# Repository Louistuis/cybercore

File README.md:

# CyberCore

**Open-hardware proof of concept: a slim black box that runs a frontier open LLM (DeepSeek V3.1, 671B) at home.**

CyberCore is a set of KiCad designs, each generated by a script so every choice is written down. Each one says plainly what is real and what is still a placeholder.

| Part | What | State |
|---|---|---|
| [**console/**](console/) | **CyberCore Console** carrier: 4 × NVIDIA Jetson T5000 (AGX Thor), 512 GB total, 25G mesh between modules, NVMe per module, QSFP28 uplink, 12-layer black board | rev 0.2 PoC: real pin map, Molex and SFF connector grids, TI power stage, **fully routed** (0 unconnected; high-speed pairs not yet length-matched), open items listed |
| [**mgmt/**](mgmt/) | **Management board**: ESP32-S3 + I/O expanders that sequence, reset and monitor the 4 modules over ribbon cables, 4 module consoles on one USB-C | Designed, every signal level sourced from NVIDIA's docs, ERC clean, parts in stock. **Routing not finished** (6 layers, 84 connections open) |
| [**panel/**](panel/) | **Status panel**: ESP32-S3, 16 RGB LEDs, SPI display, USB-C. The console's face | rev 1.0: **routed, DRC clean, every part in stock at JLCPCB, orderable** |
| [**enclosure/**](enclosure/) | **Case**: 252 × 300 × 64 mm, front intake, 4 rear exhaust fans, STL tray + lid | Concept: fit checked, cooling budget by hand calculation |
| [**pcb/**](pcb/) | **CyberCore XL** concept: our own GPU + AMD EPYC with 3.2 TB unified memory, 22 layers | Dream board: the GPU and the AMD socket can't be built or sourced (see why inside) |
| [REAL-BUILD.md](REAL-BUILD.md) | The buy-it-today version: an 8-GPU AMD Instinct server, with power, cooling and cost | Plan |

## How fast?
DeepSeek V3.1 has 671B parameters, of which 37B are active per token. At 4-bit, that's ~400 GB of weights.
- **Console (4 × Thor, 512 GB, 4 × 273 GB/s):** an estimated 10-25 tok/s for one user. It's limited by memory bandwidth: every token has to read ~18.5 GB of weights.
- **Server (8 × AMD MI350X, 2.3 TB, 64 TB/s):** fast enough for many users, but it draws ~10-14 kW.

These are estimates from bandwidth math, not measurements. The PoC is how we find out.

## Tools
- KiCad 10, scripted through its Python (`pcbnew`)
- Freerouting 2.5 for the panel, the console and the management board
- JLCPCB parts API for the stock checks

Each folder's README has its own rebuild steps.

## Not included
NVIDIA's design guide and its pin description spreadsheet are not in this repo. They're a free download from developer.nvidia.com, and `console/make_console.py` reads them from your copy.

## License
CyberCore is **open hardware, and it stays open**.

| What | License |
|---|---|
| Hardware: KiCad boards, footprints, schematics, Gerbers, BOMs, docs | [CERN-OHL-S-2.0](LICENSE) (CERN Open Hardware Licence v2, strongly reciprocal) |
| Software: the Python generator scripts | [GPL-3.0-or-later](LICENSE-SOFTWARE) |
| The CyberCore name and logo | Not licensed: see [TRADEMARKS.md](TRADEMARKS.md) |

What that means:
- **You may** build it, change it and sell it, including commercially.
- **If you ship hardware based on it**, you must publish your modified design files under the same license, keep the credit notices, and print or include the source location.
- **The CyberCore name stays with Louis Studios.** A copy must use its own name.

**Source location:** https://github.com/Louistuis/cybercore

Hardware is provided as is: each README lists the dimensions that are not confirmed yet, so check them before you order anything.

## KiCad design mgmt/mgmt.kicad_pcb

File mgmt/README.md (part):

# CyberCore management board (rev 1.0)

The console's power and reset controller: a small black board that plugs into the **CyberCore Console** carrier with five 40-way ribbon cables.
- It switches each Jetson T5000 module on and off in NVIDIA's order.
- It holds modules in reset or recovery, and watches power-good, current and temperature.
- It gives you all four module debug consoles over one USB-C cable.

The console carrier has no logic of its own; this board is its brain.

## What it does
| Block | Parts | What it does |
|---|---|---|
| Brain | ESP32-S3-WROOM-1-N16R8 (C2913202) | Runs the sequencing in [SEQUENCING.md](SEQUENCING.md). Wi-Fi status page, USB-C (MCU) for firmware and a serial console |
| Control outputs | 5 × TCA9535PWR I/O expanders (C130204), 0x20-0x23 one per module, 0x24 system | Hold every enable and request. An ESP32 reset or firmware update never drops a running module, because the expanders stay powered and keep their outputs |
| Power-bad | 74LVC07A (C7809) per module, wired-AND | `VDDIN_PWR_BAD_N` is released only when the module's HV eFuse PG **and** MV eFuse PG **and** the firmware all agree. A dropping eFuse flags power-bad in hardware, with no firmware in the loop |
| Power-on | SN74AHCT1G08 (C113521) per module on a 5 V always-on rail | Drives `MODULE_POWER_ON` at 5 V like NVIDIA's reference (DG-12084 fig 5-7), and only while `VDDIN_PWR_BAD_N` is high |
| Reset, recovery, thermal request | 74LVC07A open-drain channels, 74LVC1G07 (C7829) | Pull `SYS_RESET_N`, `FORCE_RECOVERY_N`, `THERM_SHDN_REQ_N` low. They can only pull down, never drive a level |
| Reading the module | 2 × SN74LV4T125PWR (C90755) per module | Input-only buffers with a 1.35 V threshold and 5.5 V-tolerant inputs: they read the 1.8 V, 3.3 V and 5 V module outputs, and never feed current into a powered-down module |
| 1.8 V I/O guard | TPS22918 (C131941) per module, driven by that module's own `SYS_RESET_N` | Makes `M<m>_VIO`, the only 1.8 V source that touches the module. It is off whenever the module is in reset (NVIDIA DS-11945 table 6-2) |
| Debug UARTs | CH344Q (C2988084) on USB-C (CONSOLES) + SN74LV1T34 (C100024) per module | 4 module consoles as 4 serial ports, no firmware involved. The ESP32 listens on all four for its log |
| Module I2C | PCA9306DCUR (C33196) per module | 1.8 V module I2C3 ↔ the 3.3 V system bus (PMBus + QSFP28). Each module can be switched off the bus |
| Current | ESP32 ADC1 × 4, 10k + 100 nF per channel | HV eFuse current monitors: 1.16 V at 10 A, 1.55 V at the 13.4 A limit |
| Power | TLV75518 (C2877863) 1.8 V, TPS61222 (C116461) 5 V, both from the console's 3.3 V standby | The board takes nothing from USB, so it can never back-feed the console |
| Extras | Qwiic port (inlet temperature sensor), RESET / BOOT buttons, heartbeat LED, 4 × M3 holes | |

## Connections to the console
- **Headers:** 5 × 2×20 1.27 mm (C71827, through-hole), with the same reference designators as on the console:
  - J20-J23: modules 0-3
  - J4: SYS
- **Cables:** IDC ribbon, pin 1 to pin 1, so the pinout is identical on both ends. Odd pins carry the signals listed in `parts.py` (`MGMT` and `SYS`, copied from `console/make_console.py`); even pins are GND.
- **Power:** the board runs from the console's 3.3 V standby rail on pin 39 of every header (about 0.4 A peak with Wi-Fi transmitting).

## Signal levels: every decision and its source
| Module pin | NVIDIA says | This board | Source |
|---|---|---|---|
| MODULE_POWER_ON | Input, CMOS 5.0 V, driven low first | 5 V AND gate (5V_AO) + 100 Ω, 100k pull-down | DG-12084 table 5-1, fig 5-2 note 2, fig 5-7 / table 5-2 (5V_AO gate, PP) |
| CARRIER_POWER_ON | Output, open drain 3.3 V, 10k pull-up on module | Read directly by the expander (3.3 V), 100k pull-down | DG table 5-1 |
| SYS_RESET_N | Bidir, open drain 1.8 V, 10k to 1.8 V on module | Read via LV4T125; pulled low by a 74LVC07; drives the VIO switch; 470k pull-down | DG table 5-1, DS table 3-1 |
| VDDIN_PWR_BAD_N | Open drain 5.0 V, 10k to 5 V on module | Three 74LVC07 outputs wired-AND (HV_PG, MV_PG, firmware); read via LV4T125 (5.5 V tolerant) | DG table 5-1, 5.1.1, 5.1.4 |
| FORCE_RECOVERY_N | Input, CMOS 1.8 V, 20k to 1.8 V on module | 74LVC07 open drain only | DG table 5-1, fig 18-1, ch 18 |
| MODULE_SHDN_N | Output, CMOS 1.8 V, 10k to 1.8 V on module | Read via LV4T125 | DG table 5-1 |
| THERM_ALERT_N | Open drain "3.3 V" (DG, DS), but the schematic checklist lists a 10k pull-up to 1.8 V on the module | Read via LV4T125 (works for either level), 100k to M<m>_VIO | DG table 5-1, DS table 3-1, Schematic Checklist v1.1 "Module_Signal_Term" |
| THERM_SHDN_REQ_N | **Not described** (only in the pin spreadsheet, G59) | Read via LV4T125 + 74LVC07 pull-down, 100k to VIO; firmware leaves it alone | Pin Descriptions v1.0 only |
| MODULE_POWER_GOOD | **Not described** (only in the pin spreadsheet, L59) | Read only via LV4T125, 100k pull-down | Pin Descriptions v1.0 only |
| PRSNT0 / PRSNT1 | Tied together on the module | PRSNT0 = GND, PRSNT1 10k to 3.3 V, read (low = seated) | DG table 5-1, fig 5-7 (PRSNT1 to 3V3_AO) |
| UART3_TX_DEBUG | Output, CMOS 1.8 V | Read via LV4T125 into the CH344Q, 100k to VIO | DG 17.2.2, table 17-3 |
| UART3_RX_DEBUG | Input, 1.8 V | SN74LV1T34 powered from VIO (off in reset, Ioff), 100 Ω; 100k pull-up on the 3.3 V side | DG table 17-3 |
| I2C3_CLK / DAT | Open drain 1.8 V, 1k to 1.8 V on module | PCA9306, VREF1 = VIO, enable through 74LVC1G07 | DG table 12-2, SP-12533 |
| HV_EN, MV_EN, SV_EN, BUCK5_EN | eFuse EN/UVLO 1.2 V (max 7 V), TPS22918 ON 1.0 V, TPS546B24A EN (max 5.5 V); 100k pull-downs on the console | 3.3 V push-pull from the expanders | TPS25982, TPS22918, TPS546B24A data sheets |
| HV_PG, MV_PG, BUCK5_PG | Open drain, 10k to 3.3 V on the console | Read directly + feed the power-bad AND | console/make_console.py |
| HV_IMON | 246 uA/A × 470 Ω | 10k + 100 nF into ESP32 ADC1 (0-3.1 V at 12 dB) | TPS25982 7.3.5 (10k series recommended) |
| QSFP sideband | 3.3 V LVTTL | Direct; 10k host pull-ups on ModPrsL and IntL | SFF-8679 |

**The one rule behind the table:** no 1.8 V module input is ever driven high while that module's `SYS_RESET_N` is low (DS-11945 table 6-2, VM_PIN).
- The only push-pull driver into a 1.8 V module input, and every 1.8 V pull-up, sit on `M<m>_VIO`.
- A load switch turns `M<m>_VIO` on from the module's own `SYS_RESET_N`, and off within ~15 µs when it falls.

## Board
- 132 × 72 mm, **6 layers** (F.Cu signal + GND, In1.Cu GND plane, In2.Cu and In3.Cu signal, In4.Cu 3V3 plane, B.Cu signal + GND), 1.6 mm, **black solder mask, white silk, ENIG**, all parts on top. It started as 4 layers, but Freerouting could not finish that at this size.
- **Rules:** JLCPCB standard 6-layer (0.127 mm track and space, 0.5 / 0.25 mm vias).
- **Routing:** Freerouting.
- **DRC:** see `drc.rpt`. **ERC:** see `erc.rpt`. Results are listed under "State" below.

## State
**Real:**
- Every pin of every part, from its maker's data sheet (TI, WCH, Espressif). The pin tables are quoted in `parts.py`.
- The console interface, copied from `console/make_console.py`.
- Every signal level, checked against NVIDIA's documents (table above).
- Every part was in stock at JLCPCB on 2026-11-17 (`jlc/stock.csv`).

**Routing is not finished.** After three Freerouting runs, 84 connections are still open and about 40 tracks are necked to 0.095 mm (JLC's minimum is 0.09). `mgmt_routed.kicad_pcb` is the work in progress: finish it by hand in KiCad, or give the board more room.

**Not verified (check before ordering):**
- `THERM_SHDN_REQ_N` and `MODULE_POWER_GOOD` are only names in NVIDIA's pin spreadsheet. The board treats them safely (read, plus an optional pull-down), but their function is unknown.
- `THERM_ALERT_N`: the design guide says 3.3 V open drain, the checklist says a 1.8 V pull-up. Both levels work here.
- `MODULE_POWER_ON` VIH is not published. The board drives 5 V as NVIDIA's reference does, so the number does not matter.
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
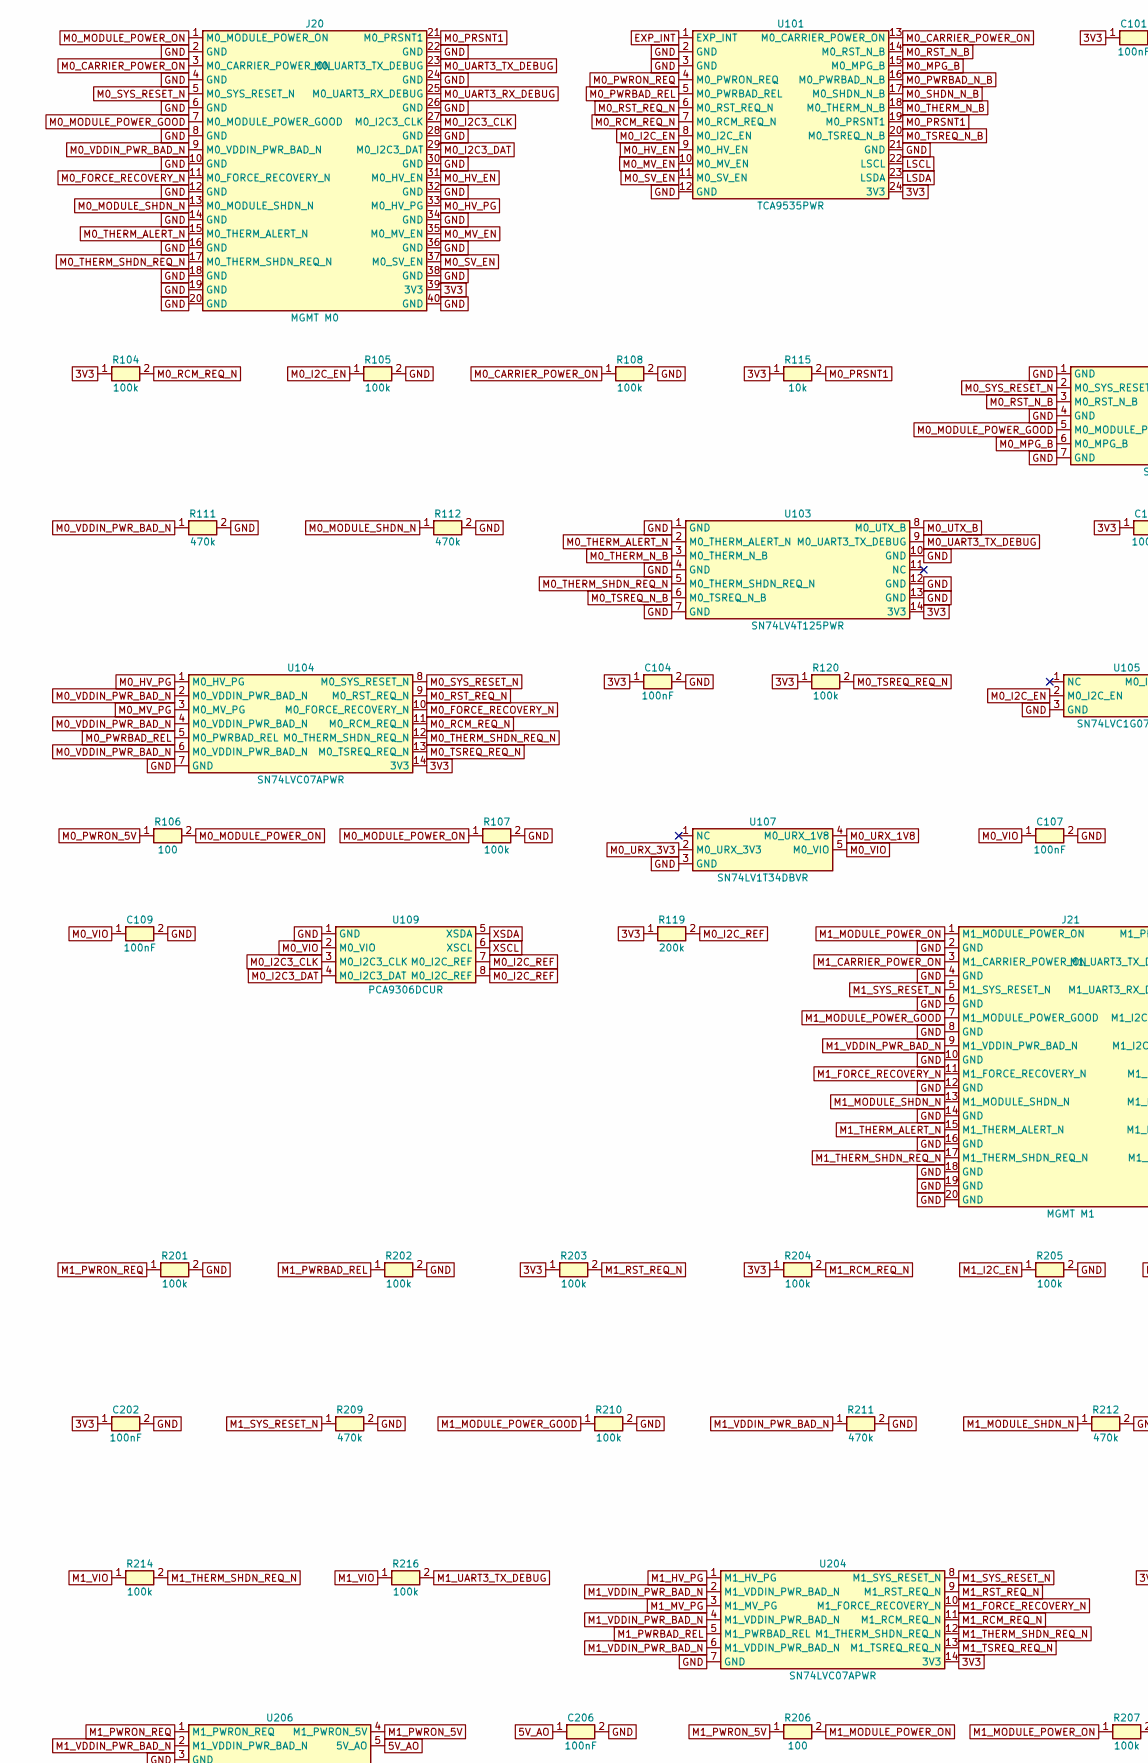
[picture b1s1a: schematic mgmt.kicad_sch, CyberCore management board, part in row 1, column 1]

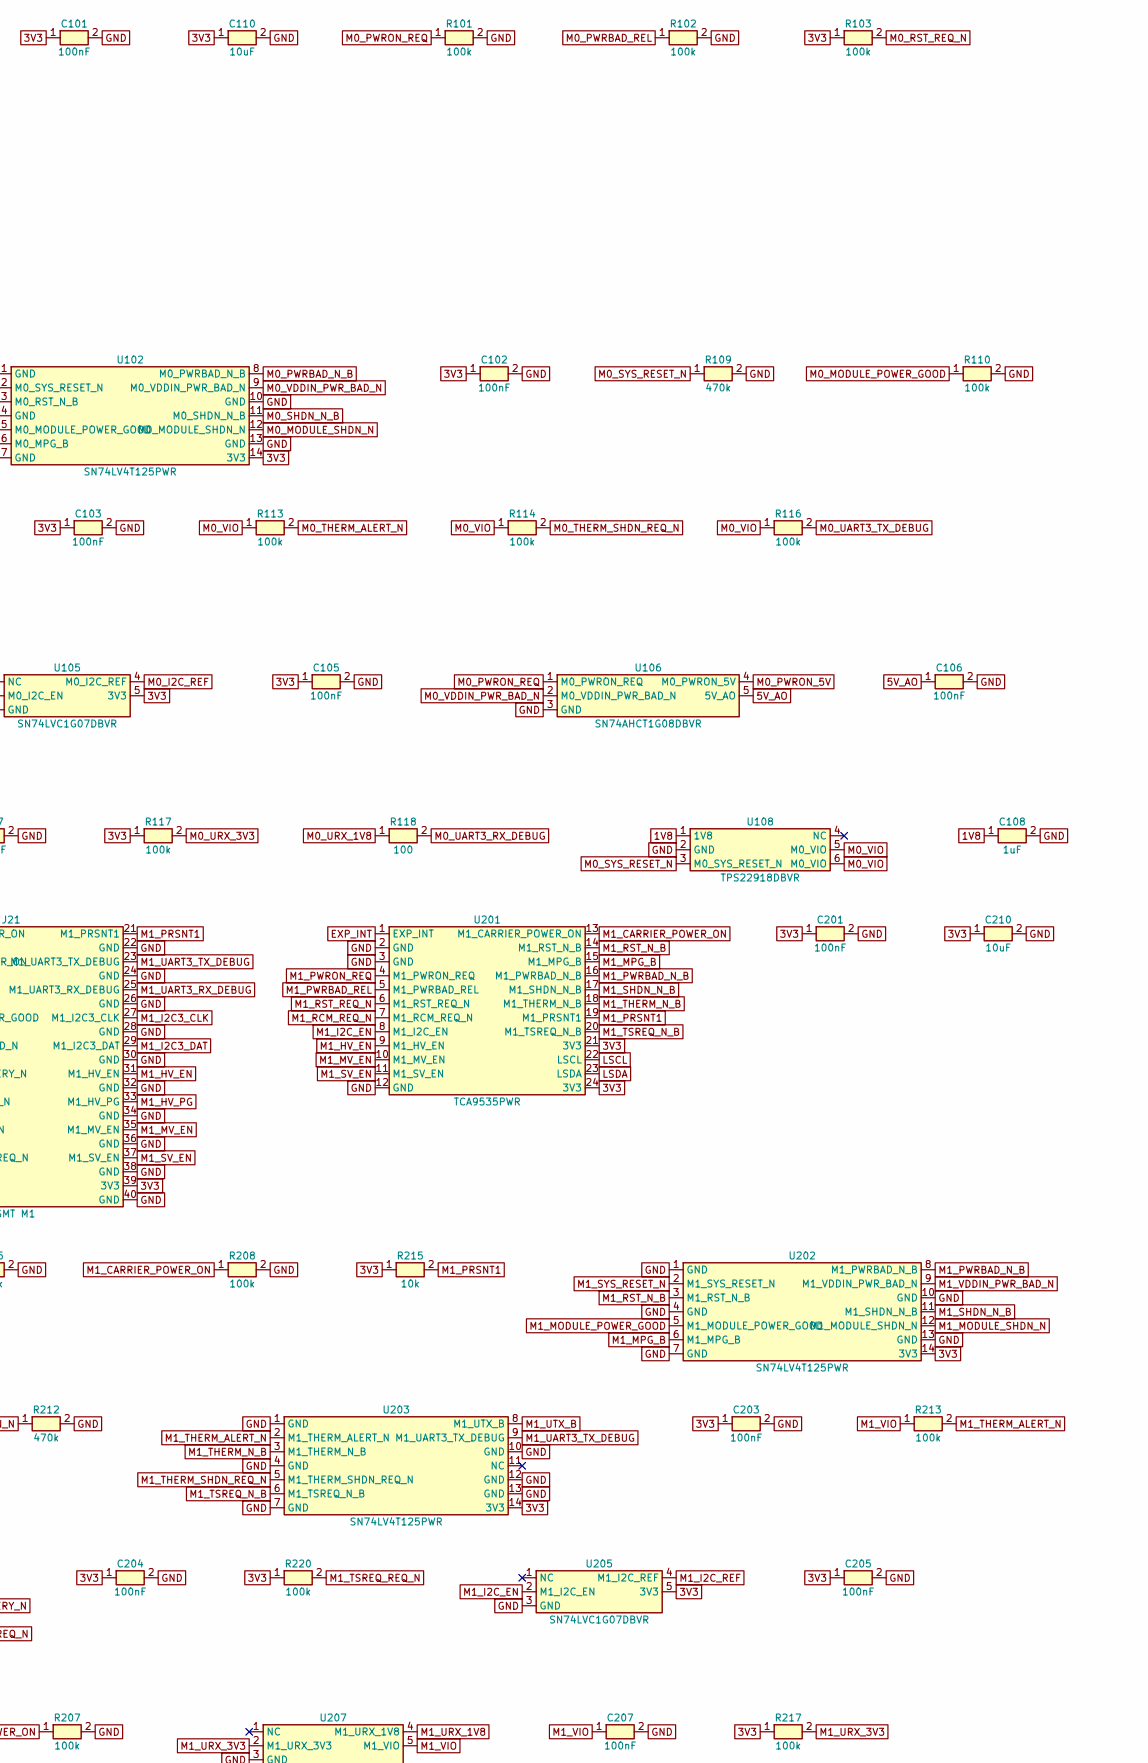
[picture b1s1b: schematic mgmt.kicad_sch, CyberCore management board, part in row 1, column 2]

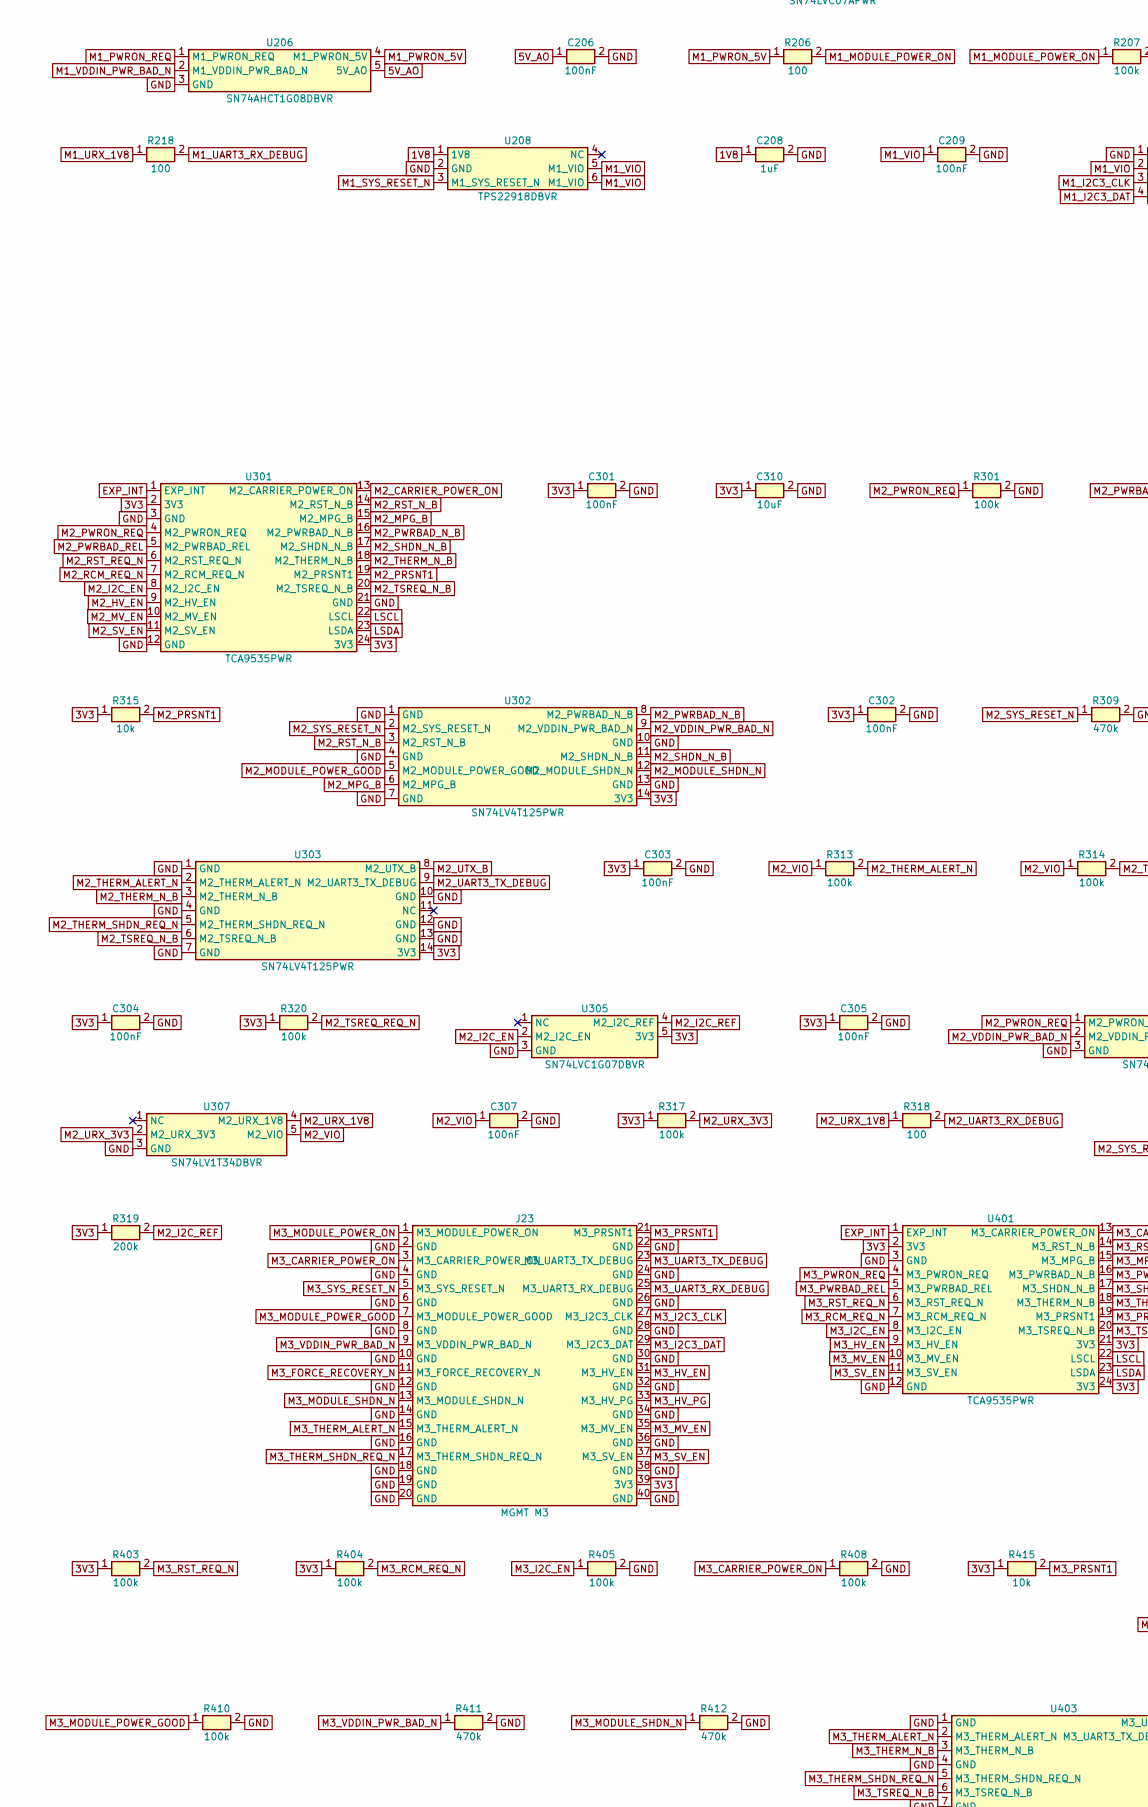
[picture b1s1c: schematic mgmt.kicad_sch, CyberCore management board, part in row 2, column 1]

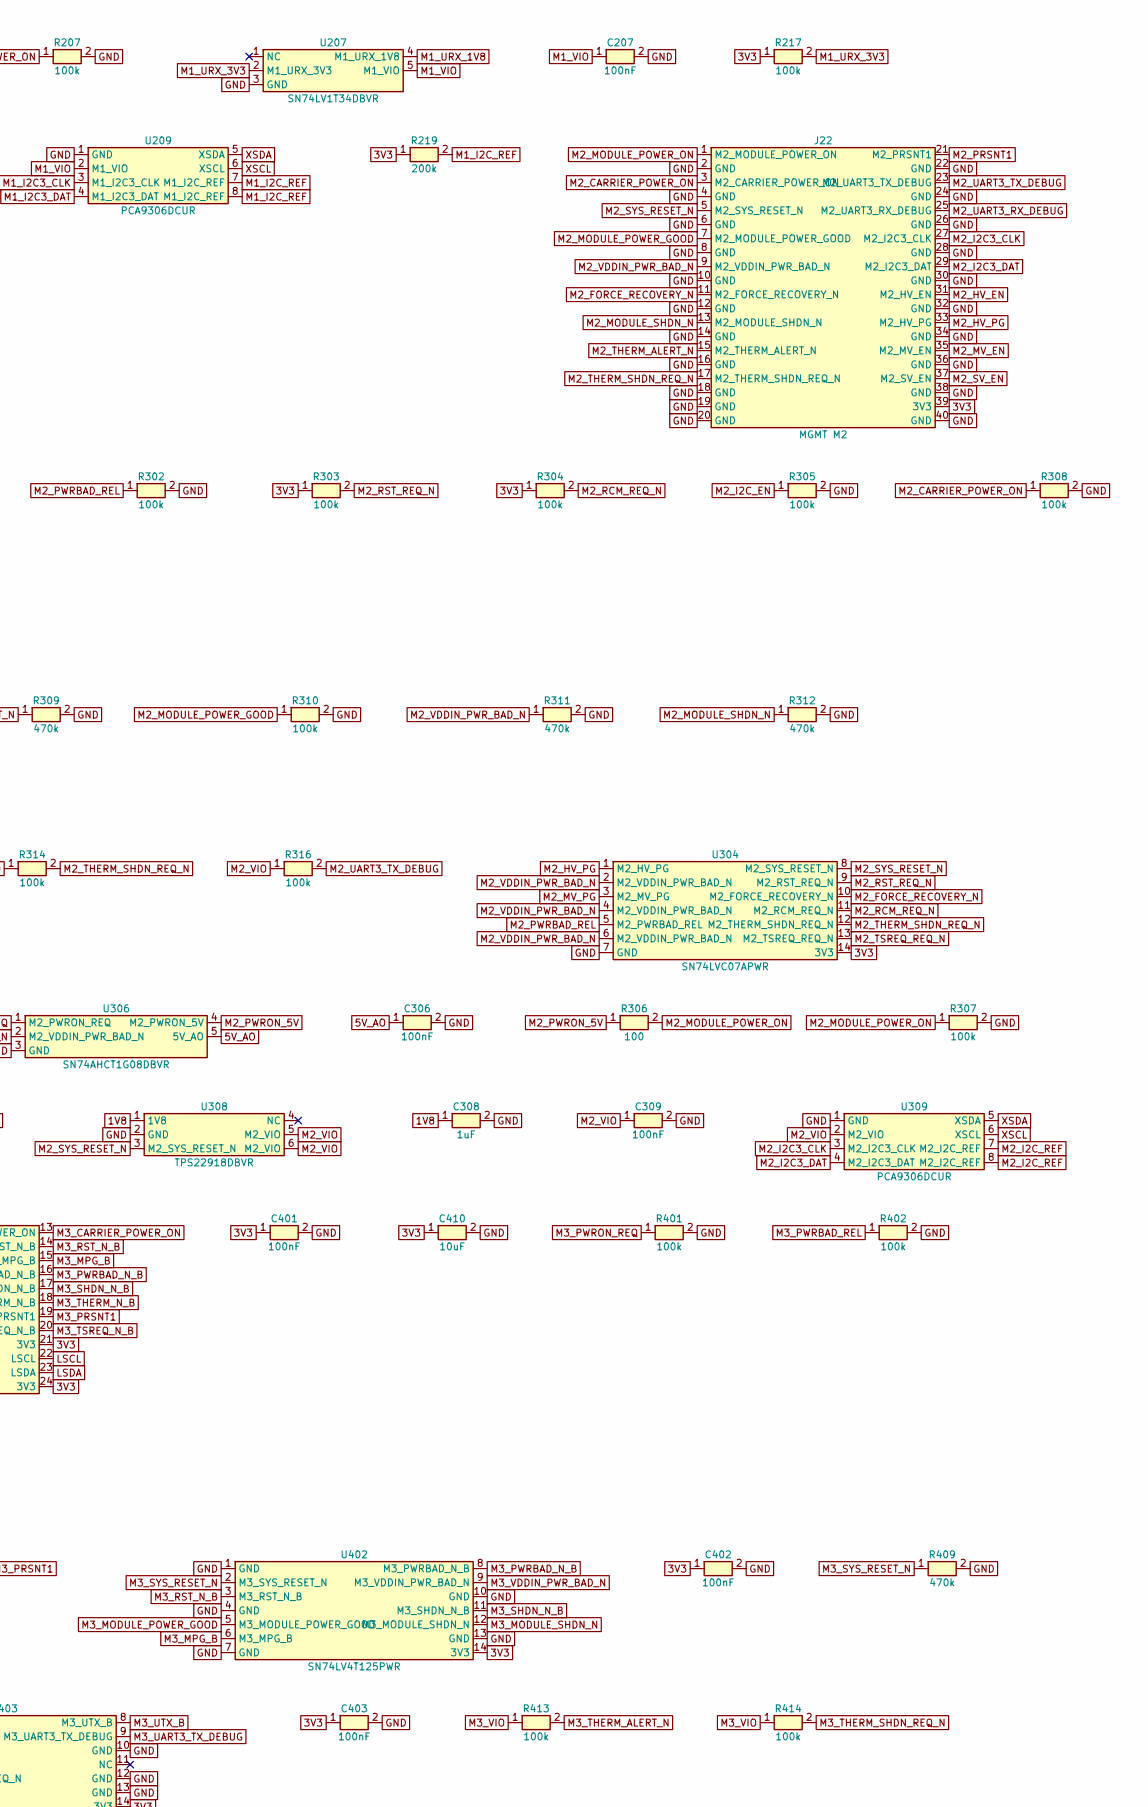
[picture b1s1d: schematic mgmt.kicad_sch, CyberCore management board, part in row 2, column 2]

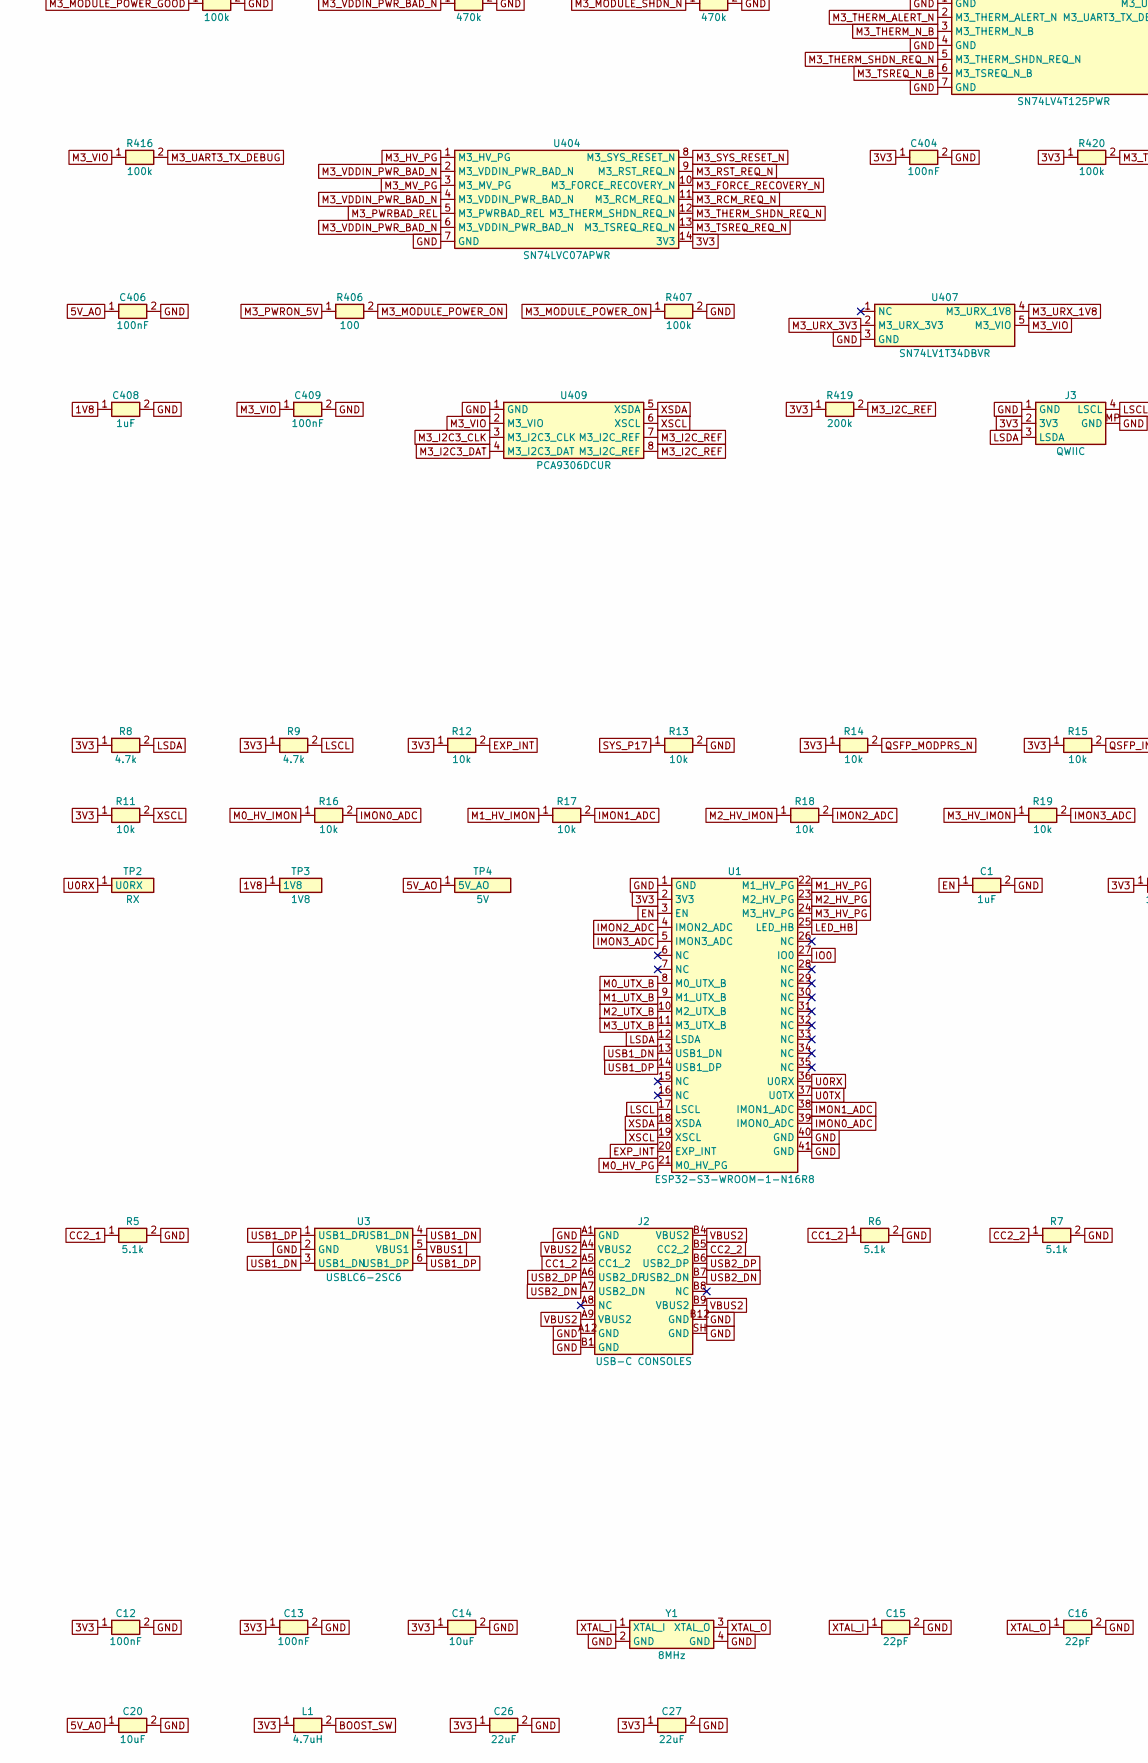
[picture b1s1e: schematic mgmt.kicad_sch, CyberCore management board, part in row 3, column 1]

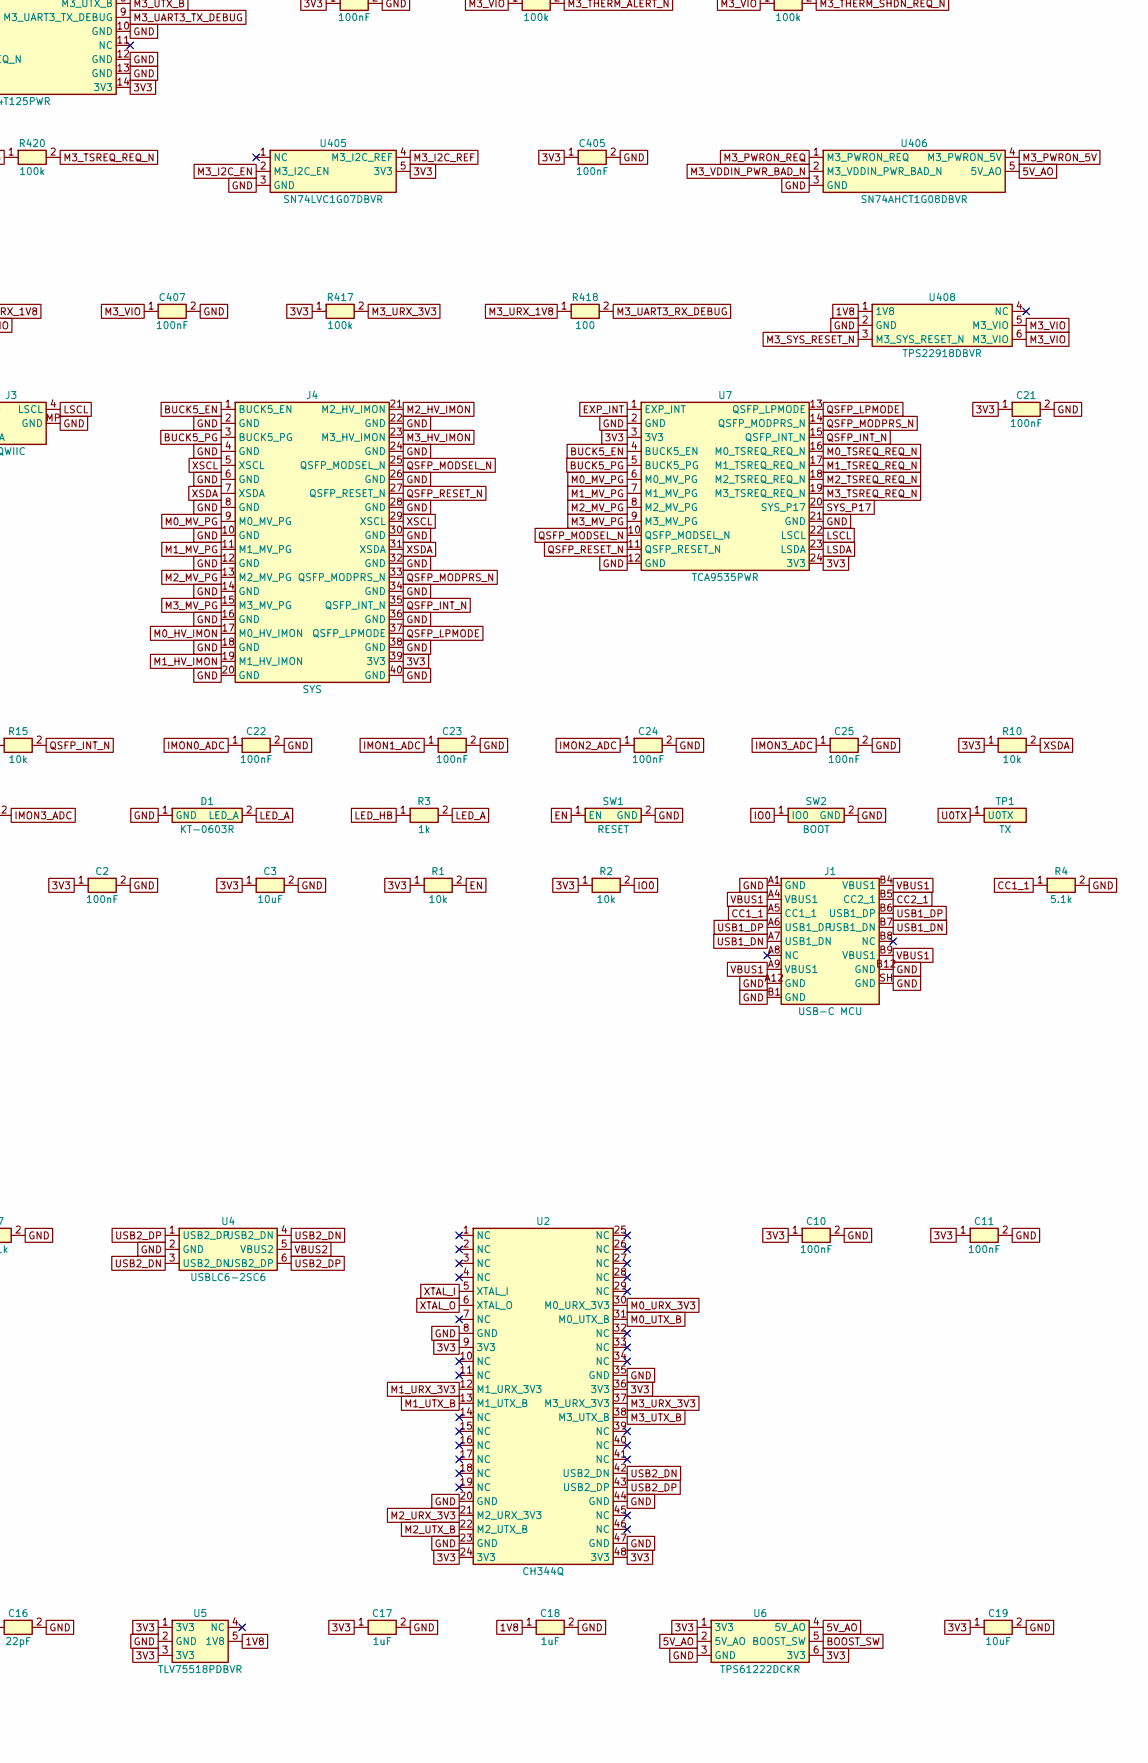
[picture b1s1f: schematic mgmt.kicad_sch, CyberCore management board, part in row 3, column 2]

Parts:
C1, C17, C18, C108, C208, C308, C408: 1uF; C_0402_1005Metric; LCSC C52923
C2, C10, C11, C12, C13, C21, C22, C23, C24, C25, C101, C102, C103, C104, C105, C106, C107, C109, C201, C202, C203, C204, C205, C206, C207, C209, C301, C302, C303, C304, C305, C306, C307, C309, C401, C402, C403, C404, C405, C406, C407, C409: 100nF; C_0402_1005Metric; LCSC C1525
C3, C14, C19, C20, C110, C210, C310, C410: 10uF; C_0603_1608Metric; LCSC C19702
C15, C16: 22pF; C_0402_1005Metric; LCSC C1555
C26, C27: 22uF; C_0805_2012Metric; LCSC C45783
D1: KT-0603R; LED_0603_1608Metric; LCSC C2286
J1: USB-C MCU; USB_C_Receptacle_HRO_TYPE-C-31-M-12; LCSC C165948
J2: USB-C CONSOLES; USB_C_Receptacle_HRO_TYPE-C-31-M-12; LCSC C165948
J3: QWIIC; JST_SH_SM04B-SRSS-TB_1x04-1MP_P1.00mm_Horizontal; LCSC C160404
J4: SYS; PinHeader_2x20_P1.27mm_Vertical; LCSC C71827
J20: MGMT M0; PinHeader_2x20_P1.27mm_Vertical; LCSC C71827
J21: MGMT M1; PinHeader_2x20_P1.27mm_Vertical; LCSC C71827
J22: MGMT M2; PinHeader_2x20_P1.27mm_Vertical; LCSC C71827
J23: MGMT M3; PinHeader_2x20_P1.27mm_Vertical; LCSC C71827
L1: 4.7uH; L_1008_2520Metric; LCSC C66536
R1, R2, R10, R11, R12, R13, R14, R15, R16, R17, R18, R19, R115, R215, R315, R415: 10k; R_0402_1005Metric; LCSC C25744
R3: 1k; R_0402_1005Metric; LCSC C11702
R4, R5, R6, R7: 5.1k; R_0402_1005Metric; LCSC C25905
R8, R9: 4.7k; R_0402_1005Metric; LCSC C25900
R101, R102, R103, R104, R105, R107, R108, R110, R113, R114, R116, R117, R120, R201, R202, R203, R204, R205, R207, R208, R210, R213, R214, R216, R217, R220, R301, R302, R303, R304, R305, R307, R308, R310, R313, R314, R316, R317, R320, R401, R402, R403, R404, R405, R407, R408, R410, R413, R414, R416, R417, R420: 100k; R_0402_1005Metric; LCSC C25741
R106, R118, R206, R218, R306, R318, R406, R418: 100; R_0402_1005Metric; LCSC C25076
R109, R111, R112, R209, R211, R212, R309, R311, R312, R409, R411, R412: 470k; R_0402_1005Metric; LCSC C25790
R119, R219, R319, R419: 200k; R_0402_1005Metric; LCSC C25764
SW1: RESET; SW_Push_1P1T_XKB_TS-1187A; LCSC C318884
SW2: BOOT; SW_Push_1P1T_XKB_TS-1187A; LCSC C318884
TP1: TX; TestPoint_Pad_D1.0mm
TP2: RX; TestPoint_Pad_D1.0mm
TP3: 1V8; TestPoint_Pad_D1.0mm
TP4: 5V; TestPoint_Pad_D1.0mm
U1: ESP32-S3-WROOM-1-N16R8; ESP32-S3-WROOM-1; LCSC C2913202
U2: CH344Q; LQFP-48_7x7mm_P0.5mm; LCSC C2988084
U3, U4: USBLC6-2SC6; SOT-23-6; LCSC C7519
U5: TLV75518PDBVR; SOT-23-5; LCSC C2877863
U6: TPS61222DCKR; SOT-363_SC-70-6; LCSC C116461
U7, U101, U201, U301, U401: TCA9535PWR; TSSOP-24_4.4x7.8mm_P0.65mm; LCSC C130204
U102, U103, U202, U203, U302, U303, U402, U403: SN74LV4T125PWR; TSSOP-14_4.4x5mm_P0.65mm; LCSC C90755
U104, U204, U304, U404: SN74LVC07APWR; TSSOP-14_4.4x5mm_P0.65mm; LCSC C7809
U105, U205, U305, U405: SN74LVC1G07DBVR; SOT-23-5; LCSC C7829
U106, U206, U306, U406: SN74AHCT1G08DBVR; SOT-23-5; LCSC C113521
U107, U207, U307, U407: SN74LV1T34DBVR; SOT-23-5; LCSC C100024
U108, U208, U308, U408: TPS22918DBVR; SOT-23-6; LCSC C131941
U109, U209, U309, U409: PCA9306DCUR; VSSOP-8_2.3x2mm_P0.5mm; LCSC C33196
Y1: 8MHz; Crystal_SMD_3225-4Pin_3.2x2.5mm; LCSC C5181477

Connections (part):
1V8: C18.1, C108.1, C208.1, C308.1, C408.1, TP3.1, U5.5 (1V8), U108.1 (1V8), U208.1 (1V8), U308.1 (1V8), U408.1 (1V8); also elsewhere on the board
3V3: C2.1, C3.1, C10.1, C11.1, C12.1, C13.1, C14.1, C17.1, C19.1, C21.1, C26.1, C27.1, C101.1, C102.1, C103.1, C104.1, C105.1, C110.1, C201.1, C202.1, C203.1, C204.1, C205.1, C210.1, C301.1, C302.1, C303.1, C304.1, C305.1, C310.1, C401.1, C402.1, C403.1, C404.1, C405.1, C410.1, J3.2 (3V3), J4.39 (3V3), J20.39 (3V3), J21.39 (3V3), J22.39 (3V3), J23.39 (3V3), L1.1, R1.1, R2.1, R8.1, R9.1, R10.1, R11.1, R12.1, R14.1, R15.1, R103.1, R104.1, R115.1, R117.1, R119.1, R120.1, R203.1, R204.1, R215.1, R217.1, R219.1, R220.1, R303.1, R304.1, R315.1, R317.1, R319.1, R320.1, R403.1, R404.1, R415.1, R417.1, R419.1, R420.1, U1.2 (3V3), U2.9 (3V3), U2.24 (3V3), U2.36 (3V3), U2.48 (3V3), U5.1 (3V3)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
5V_AO: C20.1, C106.1, C206.1, C306.1, C406.1, TP4.1, U6.2 (5V_AO), U6.4 (5V_AO), U106.5 (5V_AO), U206.5 (5V_AO), U306.5 (5V_AO), U406.5 (5V_AO)
BOOST_SW: L1.2, U6.5 (BOOST_SW)
BUCK5_EN: J4.1 (BUCK5_EN), U7.4 (BUCK5_EN)
BUCK5_PG: J4.3 (BUCK5_PG), U7.5 (BUCK5_PG)
CC1_1: J1.A5 (CC1_1), R4.1
CC1_2: J2.A5 (CC1_2), R6.1
CC2_1: J1.B5 (CC2_1), R5.1
CC2_2: J2.B5 (CC2_2), R7.1
EN: C1.1, R1.2, SW1.1 (EN), U1.3 (EN)
EXP_INT: R12.2, U1.20 (EXP_INT), U7.1 (EXP_INT), U101.1 (EXP_INT), U201.1 (EXP_INT), U301.1 (EXP_INT), U401.1 (EXP_INT)
GND: C1.2, C2.2, C3.2, C10.2, C11.2, C12.2, C13.2, C14.2, C15.2, C16.2, C17.2, C18.2, C19.2, C20.2, C21.2, C22.2, C23.2, C24.2, C25.2, C26.2, C27.2, C101.2, C102.2, C103.2, C104.2, C105.2, C106.2, C107.2, C108.2, C109.2, C110.2, C201.2, C202.2, C203.2, C204.2, C205.2, C206.2, C207.2, C208.2, C209.2, C210.2, C301.2, C302.2, C303.2, C304.2, C305.2, C306.2, C307.2, C308.2, C309.2, C310.2, C401.2, C402.2, C403.2, C404.2, C405.2, C406.2, C407.2, C408.2, C409.2, C410.2, D1.1 (GND), J1.A1 (GND), J1.A12 (GND), J1.B1 (GND), J1.B12 (GND), J1.SH (GND), J2.A1 (GND), J2.A12 (GND), J2.B1 (GND), J2.B12 (GND), J2.SH (GND), J3.1 (GND), J3.MP (GND), J4.2 (GND), J4.4 (GND), J4.6 (GND), J4.8 (GND), J4.10 (GND), J4.12 (GND), J4.14 (GND), J4.16 (GND)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; also elsewhere on the board
IMON0_ADC: C22.1, R16.2, U1.39 (IMON0_ADC)
IMON1_ADC: C23.1, R17.2, U1.38 (IMON1_ADC)
IMON2_ADC: C24.1, R18.2, U1.4 (IMON2_ADC)
IMON3_ADC: C25.1, R19.2, U1.5 (IMON3_ADC)
IO0: R2.2, SW2.1 (IO0), U1.27 (IO0)
LED_A: D1.2 (LED_A), R3.2
LED_HB: R3.1, U1.25 (LED_HB)
LSCL: J3.4 (LSCL), R9.2, U1.17 (LSCL), U7.22 (LSCL), U101.22 (LSCL), U201.22 (LSCL), U301.22 (LSCL), U401.22 (LSCL)
LSDA: J3.3 (LSDA), R8.2, U1.12 (LSDA), U7.23 (LSDA), U101.23 (LSDA), U201.23 (LSDA), U301.23 (LSDA), U401.23 (LSDA)
M0_CARRIER_POWER_ON: J20.3 (M0_CARRIER_POWER_ON), R108.1, U101.13 (M0_CARRIER_POWER_ON)
M0_FORCE_RECOVERY_N: J20.11 (M0_FORCE_RECOVERY_N), U104.10 (M0_FORCE_RECOVERY_N)
M0_HV_EN: J20.31 (M0_HV_EN), U101.9 (M0_HV_EN)
M0_HV_IMON: J4.17 (M0_HV_IMON), R16.1
M0_HV_PG: J20.33 (M0_HV_PG), U1.21 (M0_HV_PG), U104.1 (M0_HV_PG)
M0_I2C3_CLK: J20.27 (M0_I2C3_CLK), U109.3 (M0_I2C3_CLK)
M0_I2C3_DAT: J20.29 (M0_I2C3_DAT), U109.4 (M0_I2C3_DAT)
M0_I2C_EN: R105.1, U101.8 (M0_I2C_EN), U105.2 (M0_I2C_EN)
M0_I2C_REF: R119.2, U105.4 (M0_I2C_REF), U109.7 (M0_I2C_REF), U109.8 (M0_I2C_REF)
M0_MODULE_POWER_GOOD: J20.7 (M0_MODULE_POWER_GOOD), R110.1, U102.5 (M0_MODULE_POWER_GOOD)
M0_MODULE_POWER_ON: J20.1 (M0_MODULE_POWER_ON), R106.2, R107.1
M0_MODULE_SHDN_N: J20.13 (M0_MODULE_SHDN_N), R112.1, U102.12 (M0_MODULE_SHDN_N)
M0_MPG_B: U101.15 (M0_MPG_B), U102.6 (M0_MPG_B)
M0_MV_EN: J20.35 (M0_MV_EN), U101.10 (M0_MV_EN)
M0_MV_PG: J4.9 (M0_MV_PG), U7.6 (M0_MV_PG), U104.3 (M0_MV_PG)
M0_PRSNT1: J20.21 (M0_PRSNT1), R115.2, U101.19 (M0_PRSNT1)
M0_PWRBAD_N_B: U101.16 (M0_PWRBAD_N_B), U102.8 (M0_PWRBAD_N_B)
M0_PWRBAD_REL: R102.1, U101.5 (M0_PWRBAD_REL), U104.5 (M0_PWRBAD_REL)
M0_PWRON_5V: R106.1, U106.4 (M0_PWRON_5V)
M0_PWRON_REQ: R101.1, U101.4 (M0_PWRON_REQ), U106.1 (M0_PWRON_REQ)
M0_RCM_REQ_N: R104.2, U101.7 (M0_RCM_REQ_N), U104.11 (M0_RCM_REQ_N)
M0_RST_N_B: U101.14 (M0_RST_N_B), U102.3 (M0_RST_N_B)
M0_RST_REQ_N: R103.2, U101.6 (M0_RST_REQ_N), U104.9 (M0_RST_REQ_N)
M0_SHDN_N_B: U101.17 (M0_SHDN_N_B), U102.11 (M0_SHDN_N_B)
M0_SV_EN: J20.37 (M0_SV_EN), U101.11 (M0_SV_EN)
M0_SYS_RESET_N: J20.5 (M0_SYS_RESET_N), R109.1, U102.2 (M0_SYS_RESET_N), U104.8 (M0_SYS_RESET_N), U108.3 (M0_SYS_RESET_N)
M0_THERM_ALERT_N: J20.15 (M0_THERM_ALERT_N), R113.2, U103.2 (M0_THERM_ALERT_N)
M0_THERM_N_B: U101.18 (M0_THERM_N_B), U103.3 (M0_THERM_N_B)
M0_THERM_SHDN_REQ_N: J20.17 (M0_THERM_SHDN_REQ_N), R114.2, U103.5 (M0_THERM_SHDN_REQ_N), U104.12 (M0_THERM_SHDN_REQ_N)
M0_TSREQ_N_B: U101.20 (M0_TSREQ_N_B), U103.6 (M0_TSREQ_N_B)
M0_TSREQ_REQ_N: R120.2, U7.16 (M0_TSREQ_REQ_N), U104.13 (M0_TSREQ_REQ_N)
M0_UART3_RX_DEBUG: J20.25 (M0_UART3_RX_DEBUG), R118.2
M0_UART3_TX_DEBUG: J20.23 (M0_UART3_TX_DEBUG), R116.2, U103.9 (M0_UART3_TX_DEBUG)
M0_URX_1V8: R118.1, U107.4 (M0_URX_1V8)
M0_URX_3V3: R117.2, U2.30 (M0_URX_3V3), U107.2 (M0_URX_3V3)
M0_UTX_B: U1.8 (M0_UTX_B), U2.31 (M0_UTX_B), U103.8 (M0_UTX_B)
M0_VDDIN_PWR_BAD_N: J20.9 (M0_VDDIN_PWR_BAD_N), R111.1, U102.9 (M0_VDDIN_PWR_BAD_N), U104.2 (M0_VDDIN_PWR_BAD_N), U104.4 (M0_VDDIN_PWR_BAD_N), U104.6 (M0_VDDIN_PWR_BAD_N), U106.2 (M0_VDDIN_PWR_BAD_N)
M0_VIO: C107.1, C109.1, R113.1, R114.1, R116.1, U107.5 (M0_VIO), U108.5 (M0_VIO), U108.6 (M0_VIO), U109.2 (M0_VIO)
M1_CARRIER_POWER_ON: J21.3 (M1_CARRIER_POWER_ON), R208.1, U201.13 (M1_CARRIER_POWER_ON)
M1_FORCE_RECOVERY_N: J21.11 (M1_FORCE_RECOVERY_N), U204.10 (M1_FORCE_RECOVERY_N)
M1_HV_EN: J21.31 (M1_HV_EN), U201.9 (M1_HV_EN)
M1_HV_IMON: J4.19 (M1_HV_IMON), R17.1
M1_HV_PG: J21.33 (M1_HV_PG), U1.22 (M1_HV_PG), U204.1 (M1_HV_PG)
M1_I2C3_CLK: J21.27 (M1_I2C3_CLK), U209.3 (M1_I2C3_CLK)
M1_I2C3_DAT: J21.29 (M1_I2C3_DAT), U209.4 (M1_I2C3_DAT)
M1_I2C_EN: R205.1, U201.8 (M1_I2C_EN), U205.2 (M1_I2C_EN)
M1_I2C_REF: R219.2, U205.4 (M1_I2C_REF), U209.7 (M1_I2C_REF), U209.8 (M1_I2C_REF)
M1_MODULE_POWER_GOOD: J21.7 (M1_MODULE_POWER_GOOD), R210.1, U202.5 (M1_MODULE_POWER_GOOD)
M1_MODULE_POWER_ON: J21.1 (M1_MODULE_POWER_ON), R206.2, R207.1
M1_MODULE_SHDN_N: J21.13 (M1_MODULE_SHDN_N), R212.1, U202.12 (M1_MODULE_SHDN_N)
M1_MPG_B: U201.15 (M1_MPG_B), U202.6 (M1_MPG_B)
M1_MV_EN: J21.35 (M1_MV_EN), U201.10 (M1_MV_EN)
M1_MV_PG: J4.11 (M1_MV_PG), U7.7 (M1_MV_PG), U204.3 (M1_MV_PG)
M1_PRSNT1: J21.21 (M1_PRSNT1), R215.2, U201.19 (M1_PRSNT1)
M1_PWRBAD_N_B: U201.16 (M1_PWRBAD_N_B), U202.8 (M1_PWRBAD_N_B)
M1_PWRBAD_REL: R202.1, U201.5 (M1_PWRBAD_REL), U204.5 (M1_PWRBAD_REL)
M1_PWRON_5V: R206.1, U206.4 (M1_PWRON_5V)
M1_PWRON_REQ: R201.1, U201.4 (M1_PWRON_REQ), U206.1 (M1_PWRON_REQ)
M1_RCM_REQ_N: R204.2, U201.7 (M1_RCM_REQ_N), U204.11 (M1_RCM_REQ_N)
M1_RST_N_B: U201.14 (M1_RST_N_B), U202.3 (M1_RST_N_B)
M1_RST_REQ_N: R203.2, U201.6 (M1_RST_REQ_N), U204.9 (M1_RST_REQ_N)
M1_SHDN_N_B: U201.17 (M1_SHDN_N_B), U202.11 (M1_SHDN_N_B)
M1_SV_EN: J21.37 (M1_SV_EN), U201.11 (M1_SV_EN)
M1_SYS_RESET_N: J21.5 (M1_SYS_RESET_N), R209.1, U202.2 (M1_SYS_RESET_N), U204.8 (M1_SYS_RESET_N), U208.3 (M1_SYS_RESET_N)
M1_THERM_ALERT_N: J21.15 (M1_THERM_ALERT_N), R213.2, U203.2 (M1_THERM_ALERT_N)
M1_THERM_N_B: U201.18 (M1_THERM_N_B), U203.3 (M1_THERM_N_B)
M1_THERM_SHDN_REQ_N: J21.17 (M1_THERM_SHDN_REQ_N), R214.2, U203.5 (M1_THERM_SHDN_REQ_N), U204.12 (M1_THERM_SHDN_REQ_N)
M1_TSREQ_N_B: U201.20 (M1_TSREQ_N_B), U203.6 (M1_TSREQ_N_B)
M1_TSREQ_REQ_N: R220.2, U7.17 (M1_TSREQ_REQ_N), U204.13 (M1_TSREQ_REQ_N)
M1_UART3_RX_DEBUG: J21.25 (M1_UART3_RX_DEBUG), R218.2
M1_UART3_TX_DEBUG: J21.23 (M1_UART3_TX_DEBUG), R216.2, U203.9 (M1_UART3_TX_DEBUG)
M1_URX_1V8: R218.1, U207.4 (M1_URX_1V8)
M1_URX_3V3: R217.2, U2.12 (M1_URX_3V3), U207.2 (M1_URX_3V3)
M1_UTX_B: U1.9 (M1_UTX_B), U2.13 (M1_UTX_B), U203.8 (M1_UTX_B)
M1_VDDIN_PWR_BAD_N: J21.9 (M1_VDDIN_PWR_BAD_N), R211.1, U202.9 (M1_VDDIN_PWR_BAD_N), U204.2 (M1_VDDIN_PWR_BAD_N), U204.4 (M1_VDDIN_PWR_BAD_N), U204.6 (M1_VDDIN_PWR_BAD_N), U206.2 (M1_VDDIN_PWR_BAD_N)
M1_VIO: C207.1, C209.1, R213.1, R214.1, R216.1, U207.5 (M1_VIO), U208.5 (M1_VIO), U208.6 (M1_VIO), U209.2 (M1_VIO)
M2_CARRIER_POWER_ON: J22.3 (M2_CARRIER_POWER_ON), R308.1, U301.13 (M2_CARRIER_POWER_ON)
M2_FORCE_RECOVERY_N: J22.11 (M2_FORCE_RECOVERY_N), U304.10 (M2_FORCE_RECOVERY_N)
M2_HV_EN: J22.31 (M2_HV_EN), U301.9 (M2_HV_EN)
M2_HV_IMON: J4.21 (M2_HV_IMON), R18.1
M2_HV_PG: J22.33 (M2_HV_PG), U1.23 (M2_HV_PG), U304.1 (M2_HV_PG)
M2_I2C3_CLK: J22.27 (M2_I2C3_CLK), U309.3 (M2_I2C3_CLK)
M2_I2C3_DAT: J22.29 (M2_I2C3_DAT), U309.4 (M2_I2C3_DAT)
M2_I2C_EN: R305.1, U301.8 (M2_I2C_EN), U305.2 (M2_I2C_EN)
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
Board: 6 copper layers, 225 parts (0 on the bottom side), 192 nets, no tracks yet.

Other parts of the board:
H1, H2, H3, H4: M3; MountingHole_3.2mm_M3
R20: 10k; R_0402_1005Metric

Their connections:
1V8: R20.1; also elsewhere on the board
GND: R20.2; also elsewhere on the board

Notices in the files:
console/make_console.py:
SPDX-License-Identifier: GPL-3.0-or-later
Copyright (c) 2026 Louis Studios. Part of CyberCore: https://github.com/Louistuis/cybercore
mgmt/mgmt.kicad_pcb:
ESP32-S3  |  power sequencing for 4 x Jetson T5000  |  CERN-OHL-S-2.0
